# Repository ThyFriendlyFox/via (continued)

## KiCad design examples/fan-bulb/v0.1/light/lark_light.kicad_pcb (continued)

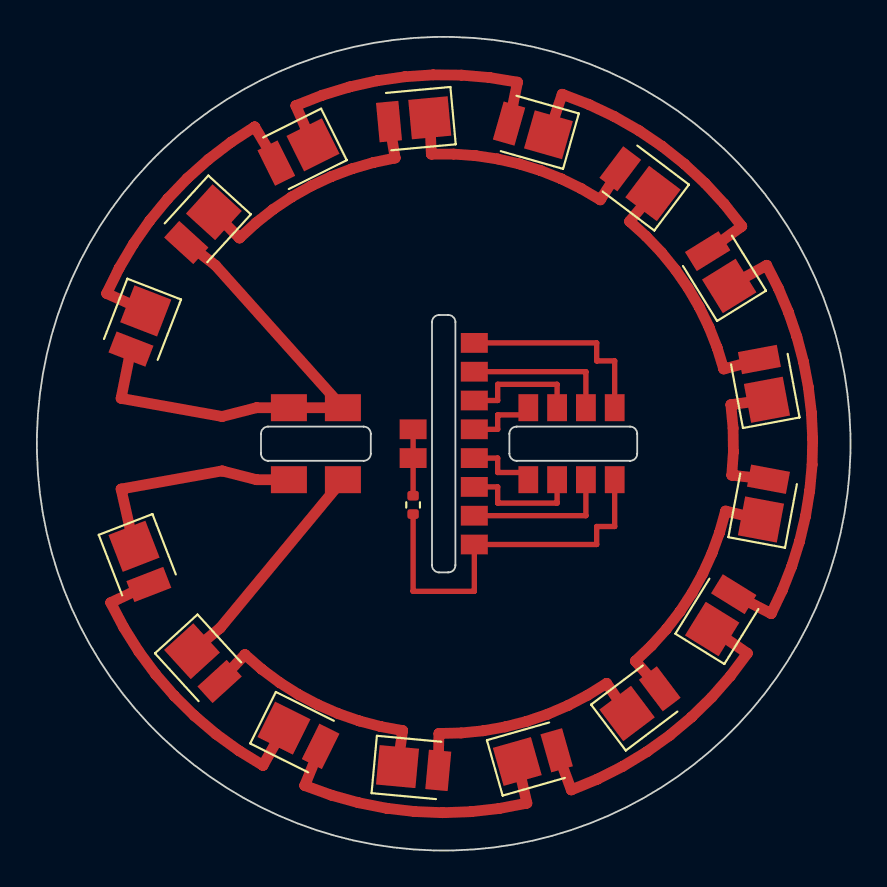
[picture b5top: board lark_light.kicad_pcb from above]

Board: 2 copper layers, 45.2 x 45.2 mm, 23 parts (0 on the bottom side), 26 nets.

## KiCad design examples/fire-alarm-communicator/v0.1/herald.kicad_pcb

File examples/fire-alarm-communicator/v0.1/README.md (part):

# Herald v0.1: a fire alarm communicator

Herald sits in a cabinet beside a fire alarm control panel and reports what the panel reports to a
monitoring station: over LTE-M first, over Wi-Fi when the cell path is down. It takes the panel's
signals 2 ways. It answers the panel's own phone dialer as if it were the phone line, and it reads
3 supervised relay contacts. A relay tells the panel when Herald itself is in trouble.

This folder is a whole KiCad 10 project made with Via: `design.py` is the board,
and the `.kicad_*` files beside it are what `workcenter design` writes from it. It is one of
Via's example projects, laid out the way a board repository lays out a version.

<!-- pictures:begin -->

| Front | Back |
|---|---|
|  |  |

| Every layer | The schematic, wired, in blocks |
|---|---|
|  |  |

From `workcenter render . --strict --views schematic,3d,layers,spin --width 1600 --spin-zoom 1.1`,
with KiCad's 3D bodies in `KICAD10_3DMODEL_DIR` (Via's `site/media/README.md` says how to
fetch them) and the 3 bodies in `models/`.
<!-- pictures:end -->

## What is hard about it, and where each part lives

| The problem | The answer on this board |
|---|---|
| A fire panel reports by phone, and there is no phone line | J2 is the panel dialer's line. Q3 (BCP53) and Q4 (MMBT3906) feed it a current-limited loop from the 24 V input: Q4 holds 0.55-0.75 V across R18 (27 ohm), 20 to 28 mA. R22 (47 ohm) in the return reads the loop current, so the ESP32 sees the dialer go off hook. The ESP32 then plays dial tone, the handshake and the kissoff from a PWM pin through 2 RC poles (R25-R27, C26-C28), and hears the dialer's DTMF digits on an ADC pin through C29 and R28 onto a mid-rail bias. `sim/tone_out.cir` and `sim/dtmf_in.cir` hold each level at every corner. |
| DTMF without a DTMF chip | `firmware/src/dtmf.c` runs a Goertzel filter per DTMF frequency over 25.6 ms windows, 12.8 ms apart, at 8 kHz. It takes and refuses what ITU-T Q.24 (Table A-1) says a receiver must: 0 to -25 dBm, the high tone 4 dB over to 8 dB under the low one, 1.5 % off frequency but not 3.5 %, 40 ms digits but not 23 ms ones. The host tests play all 16 keys and a whole Contact ID call through it. |
| A panel that reports by relay | 3 supervised inputs on J3. Each loop ends in a 4.7k resistor across the panel's contact, so the ADC tells a closed contact, a whole loop and a cut wire apart. R32 (4.7k) pulls each loop up, R31 (100) meets the field wiring, U8 clamps it. `sim/zone_*.cir` hold every reading 200 mV or more from the firmware's thresholds at every corner. |
| The panel must know when Herald fails | K1 (Omron G6K-2F-Y) is held on while Herald is healthy. A lost supply opens it, and so does a reset: R46 holds Q6 off until the firmware drives it. The panel sees its supervisory or trouble input change. Both poles run in parallel. |
| 2 paths to the station | U3, a Quectel BG95-M1 (LTE-M), with its nano SIM (J5) and antenna connector (J4). The ESP32-S3's own Wi-Fi is the second path; its antenna is on the module's u.FL. The BG95's I/O is 1.8 V: U4 (TXS0104E) carries its UART, STATUS and RI to the ESP32's 3.3 V. |
| When neither path works | Q5 (LINE_EN) lets the firmware drop the line feed. The panel then sees no phone line and reports its own communication trouble, the way it would for a cut line. R21 holds the feed off while the ESP32 is in reset. |
| The panel's 0 V must not touch the cabinet | A fire panel watches for an earth fault: any path from its wiring to earth. The 4 mounting holes are bare, and nothing ties GND to them. The back of the board says so. |

## The board

- 84.4 x 64 mm, 4 layers, 1.6 mm: F.Cu signal and a GND pour, In1.Cu a whole GND plane, In2.Cu
  signal, B.Cu signal and a GND pour. Every part is on the front. Order it as 4 layers.
- Red solder mask, white legend, ENIG: `design.py`'s `HeraldDesign` writes the colours into the
  stackup, and `workcenter render` draws the board in them.
- The field wiring enters along the bottom edge: 24 V in, the phone line, the 3 inputs and their
  common, the trouble relay's contacts, and the cabinet's tamper switch. Each terminal block's
  wire entry faces the edge.
- The status lights (power, cell, Wi-Fi, alarm, trouble), the USB-C port for set-up and the TEST
  and RESET buttons sit on the right edge; the LTE antenna connector in the top-left corner.
- The antenna feed from the BG95's pad 60 to J4 is drawn by hand, 0.35 mm: 50 ohm over In1.Cu.

### Power

J1 takes the panel's 24 V auxiliary output, 18 to 28 V. F1 (a PTC) and D1 (SMAJ28A) come first: a
surge is clamped, and a supply wired backwards drives D1 forward until F1 trips. D2 (SS34) keeps the
reversed voltage off everything else. U1 (LMR33630, 3 A, 400 kHz) makes +3V8 for the modem; U2
(TLV75733P, 1 A) makes +3V3 from it. The BG95 makes its own +1V8 (VDD_EXT) for its I/O. USB's
5 V reaches the buck through D3, so the board runs on a laptop for set-up. R3 and R4 let the ESP32
read the input.

### The ESP32-S3's pins

| GPIO | Net | To |
|---|---|---|
| 0 | IO0 | the boot strap, held high by R14 |
| 1, 2, 4 | ZONE1_ADC, ZONE2_ADC, ZONE3_ADC | the 3 inputs (ADC1 channels 0, 1, 3) |
| 3 | IO3 | a strapping pin with no pull of its own, held low by R17 |
| 5 | LOOP_ADC | the off-hook sense, R23 from RING (ADC1 channel 4) |
| 6 | VSENSE | the 24 V input through R3/R4 (ADC1 channel 5) |
| 7 | DTMF_ADC | the DTMF input (ADC1 channel 6) |
| 8, 9 | PWRKEY_CTL, RESET_CTL | Q1 and Q2, the BG95's PWRKEY and RESET_N |
| 10, 11 | ESP_TXD, ESP_RXD | the BG95's UART through U4 |
| 12, 13 | STATUS_3V3, RI_3V3 | the BG95's STATUS and RI through U4 |
| 14 | TONE | the tone path (LEDC PWM) |
| 15 | LINE_EN | Q5: the line feed on |
| 16 | RELAY_DRV | Q6: the trouble relay |
| 17 | TAMPER | J8, the cabinet's tamper switch |
| 19, 20 | USB_DN, USB_DP | J6 through U7 |
| 35-38 | LED_CELL, LED_WIFI, LED_ALARM, LED_TRBL | D8-D11 |
| 39 | BTN_TEST | SW1 |

The checks beside the table (`PROCESSES.md` P16): every analog input is on ADC1, because ADC2 is
shared with Wi-Fi (ESP-IDF, "ADC Oneshot", Hardware Limitations). GPIO26 is the PSRAM's on the
N4R2 variant and is left free (datasheet v1.7, Table 3-1, note b). GPIO45 and GPIO46 are straps and
are left to their internal pull-downs (Table 4-1). GPIO3 must not float (section 4.4): R17.

### Connectors

| Ref | Part | Pins |
|---|---|---|
| J1 | Phoenix PT 1,5/ 2-3,5-H BK, 3.5 mm, 2-way, black | 1 +24V (VFACP), 2 0V |
| J2 | Phoenix PT 1,5/ 2-3,5-H BK, 3.5 mm, 2-way, black | 1 TIP (through F2), 2 RING |
| J3 | Phoenix PT 1,5/ 4-3,5-H BK, 3.5 mm, 4-way, black | 1 ALM, 2 SUP, 3 TBL, 4 0V: the 3 loops' common |
| J7 | Phoenix PT 1,5/ 3-3,5-H BK, 3.5 mm, 3-way, black | 1 NC, 2 C, 3 NO of K1 (C to NO closed while healthy) |
| J8 | Phoenix PT 1,5/ 2-3,5-H BK, 3.5 mm, 2-way, black | 1 TAMP, 2 0V: the cabinet door's switch, closed while shut |
| J6 | GCT USB4085, through-hole | VBUS through D3 to the buck, D+/D- to the ESP32, CC1/CC2 5.1k to GND (a device) |
| J4 | Hirose U.FL | the BG95's main antenna |
| J5 | Same Sky NSIM-2-C, hinged | the BG95's USIM: VCC, RST, CLK, I/O through 22 ohm (R9-R11) |

## The call

What the dialer and Herald say to each other, with the firmware's constant for each
(`firmware/src/contactid.h`). The SIA DC-05 text was not read: the values come from 2 open
receivers (spandsp's `ademco_contactid.c`, Asterisk's `app_alarmreceiver.c`), the Zeta ZNDC fire
dialer's manual (5.2-5.3) and DMP's LT-1462, which cites DC-05-1999.09.

| Step | Who | What |
|---|---|---|
| Seize | the dialer | goes off hook: the loop current reads 0.78 V or more on GPIO5 for 20 ms (`LINE_STABLE`) |
| Dial tone | Herald | North America's 350 + 440 Hz, until the first digit |
| Dial | the dialer | the station's number in DTMF; 1.5 s of quiet ends it (`DIAL_GAP_MS`) |
| Handshake | Herald | 1400 Hz 100 ms, silence 100 ms, 2300 Hz 100 ms |
| Message | the dialer | 16 DTMF digits, 50-60 ms on and off: ACCT MT Q XYZ GG CCC S. The values' sum, 0 counted as 10, is a multiple of 15; 11-15 go as `*`, `#`, `A`, `B`, `C` |
| Kissoff | Herald | 1400 Hz for 800 ms after a good message (`KISSOFF_MS`); none after a bad one, so the dialer sends it again |

Fire panels' common event codes: 110 fire alarm, 200 fire supervisory, 300 system trouble, 301 AC
loss, 373 fire trouble, 602 periodic test (Q 1 a new event, 3 a restore).

## What proves it

```sh
workcenter design design.py --route    # the KiCad project, routed: from this folder
workcenter gates .                     # ERC, DRC, SIM, EXPORT
make -C firmware test                  # the inputs, the hook, DTMF and Contact ID on the host
```

- **The gates.** `GREEN with 7 warnings`: ERC 0 errors and 0 warnings; DRC 0 errors and 0
  unconnected, the 7 warnings the silkscreen of the 5 terminal blocks and the USB receptacle
  (2 lines) reaching the edge they face; SIM 8 decks, 573 corner runs; EXPORT 4 of 4 outputs,
  24 gerber files in `build/fab/`.
- **The route.** FreeRouting joins every net but 3, drawn by hand. It found no way for K1's NO
  contact past the strip that keeps tracks off the terminals' names, and took the C contact round
  the relay's label: both run on the front straight down to a via clear of the legend, then on
  In2.Cu under the strip to J7. Left to the router, D+ walled J6's A5 pin in, so CC1 runs from R15
  straight down and across into A5, between D+ and VBUS. A ground via beside 4 pads (U5.63,
  C24.2, J5.SH, C13.2) is placed before the route, so no route walls them off the front pour.
  `workcenter inspect probe` on the routed board finds each track clear and each via meeting only
  itself, and the DRC agrees. Keep-outs hold copper off every word: the front's
  under the mark, the terminals', the lights' and the buttons' names; the back's under the mark,
  the name, the subtitles, the write-on boxes and each terminal group's 2 lines.
- **The supervised inputs, simulated.** `sim/zone_short.cir`, `sim/zone_normal.cir`,
  `sim/zone_normal_wire.cir` and `sim/zone_open.cir` put a closed contact, a whole loop with and
  without 100 ohm of wire, and a cut wire on zone 1, each with 1 uA of leakage pushing toward the
  nearest threshold. The corners (`sim/corners.json`) run 0 and 50 C, every resistor at both ends
  of 1 %, the end-of-line resistor at 5 %, +3V3 at 3 %, and 32 Monte Carlo draws. The worst
  readings: a closed contact 0.151 V, a whole loop 1.555 to 1.798 V, a cut wire 3.186 V; each
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
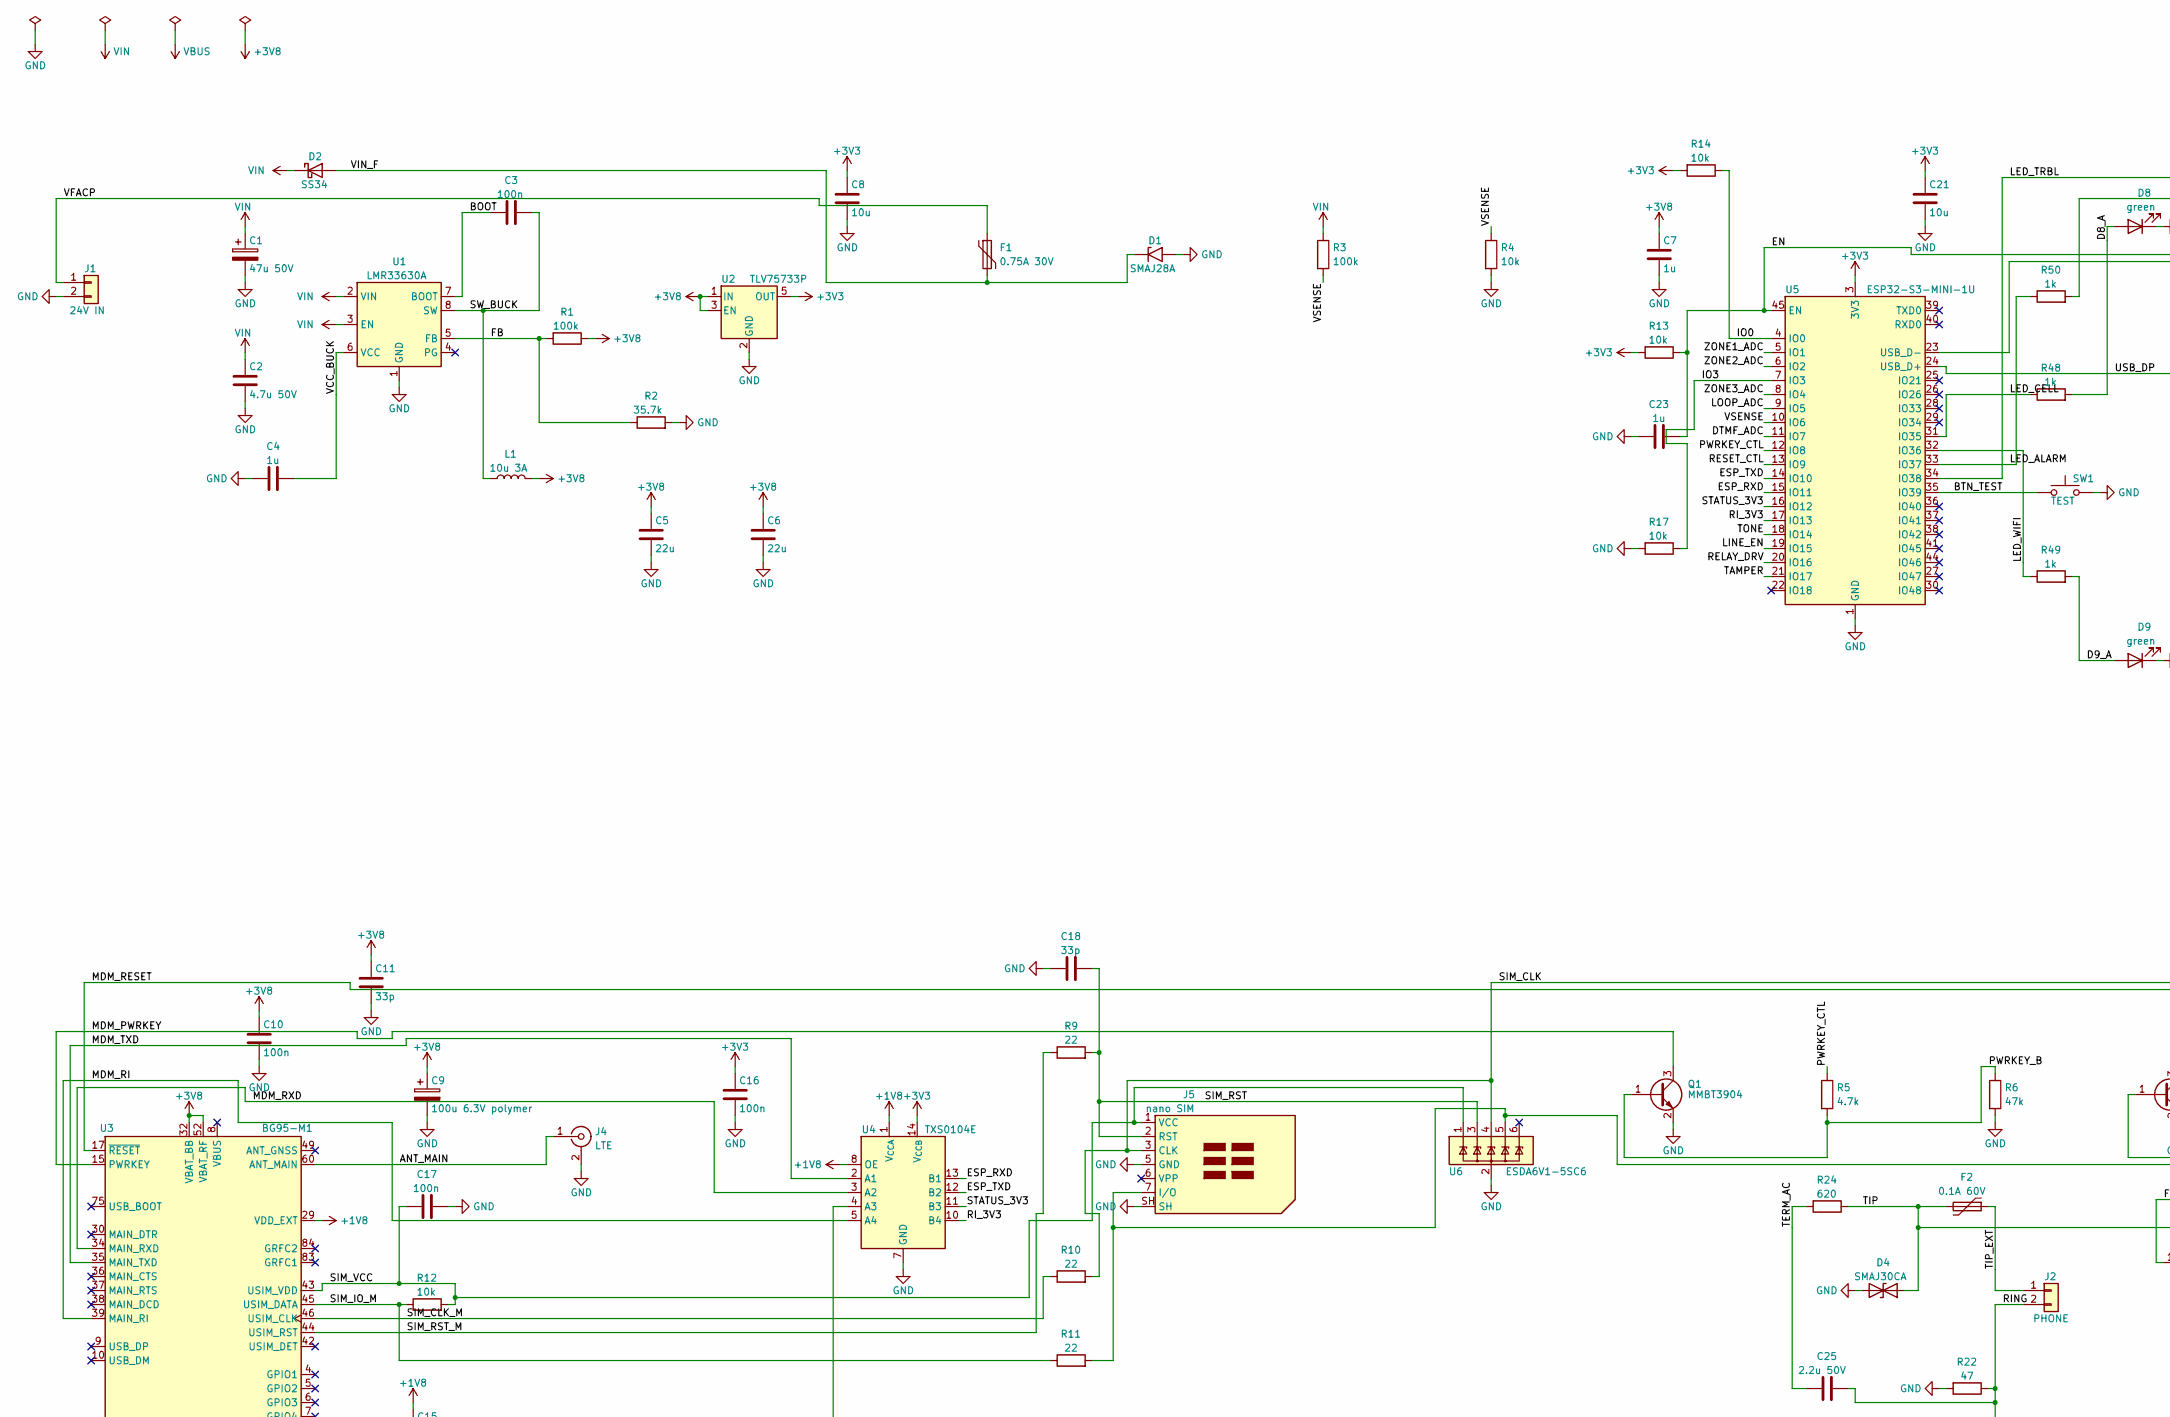
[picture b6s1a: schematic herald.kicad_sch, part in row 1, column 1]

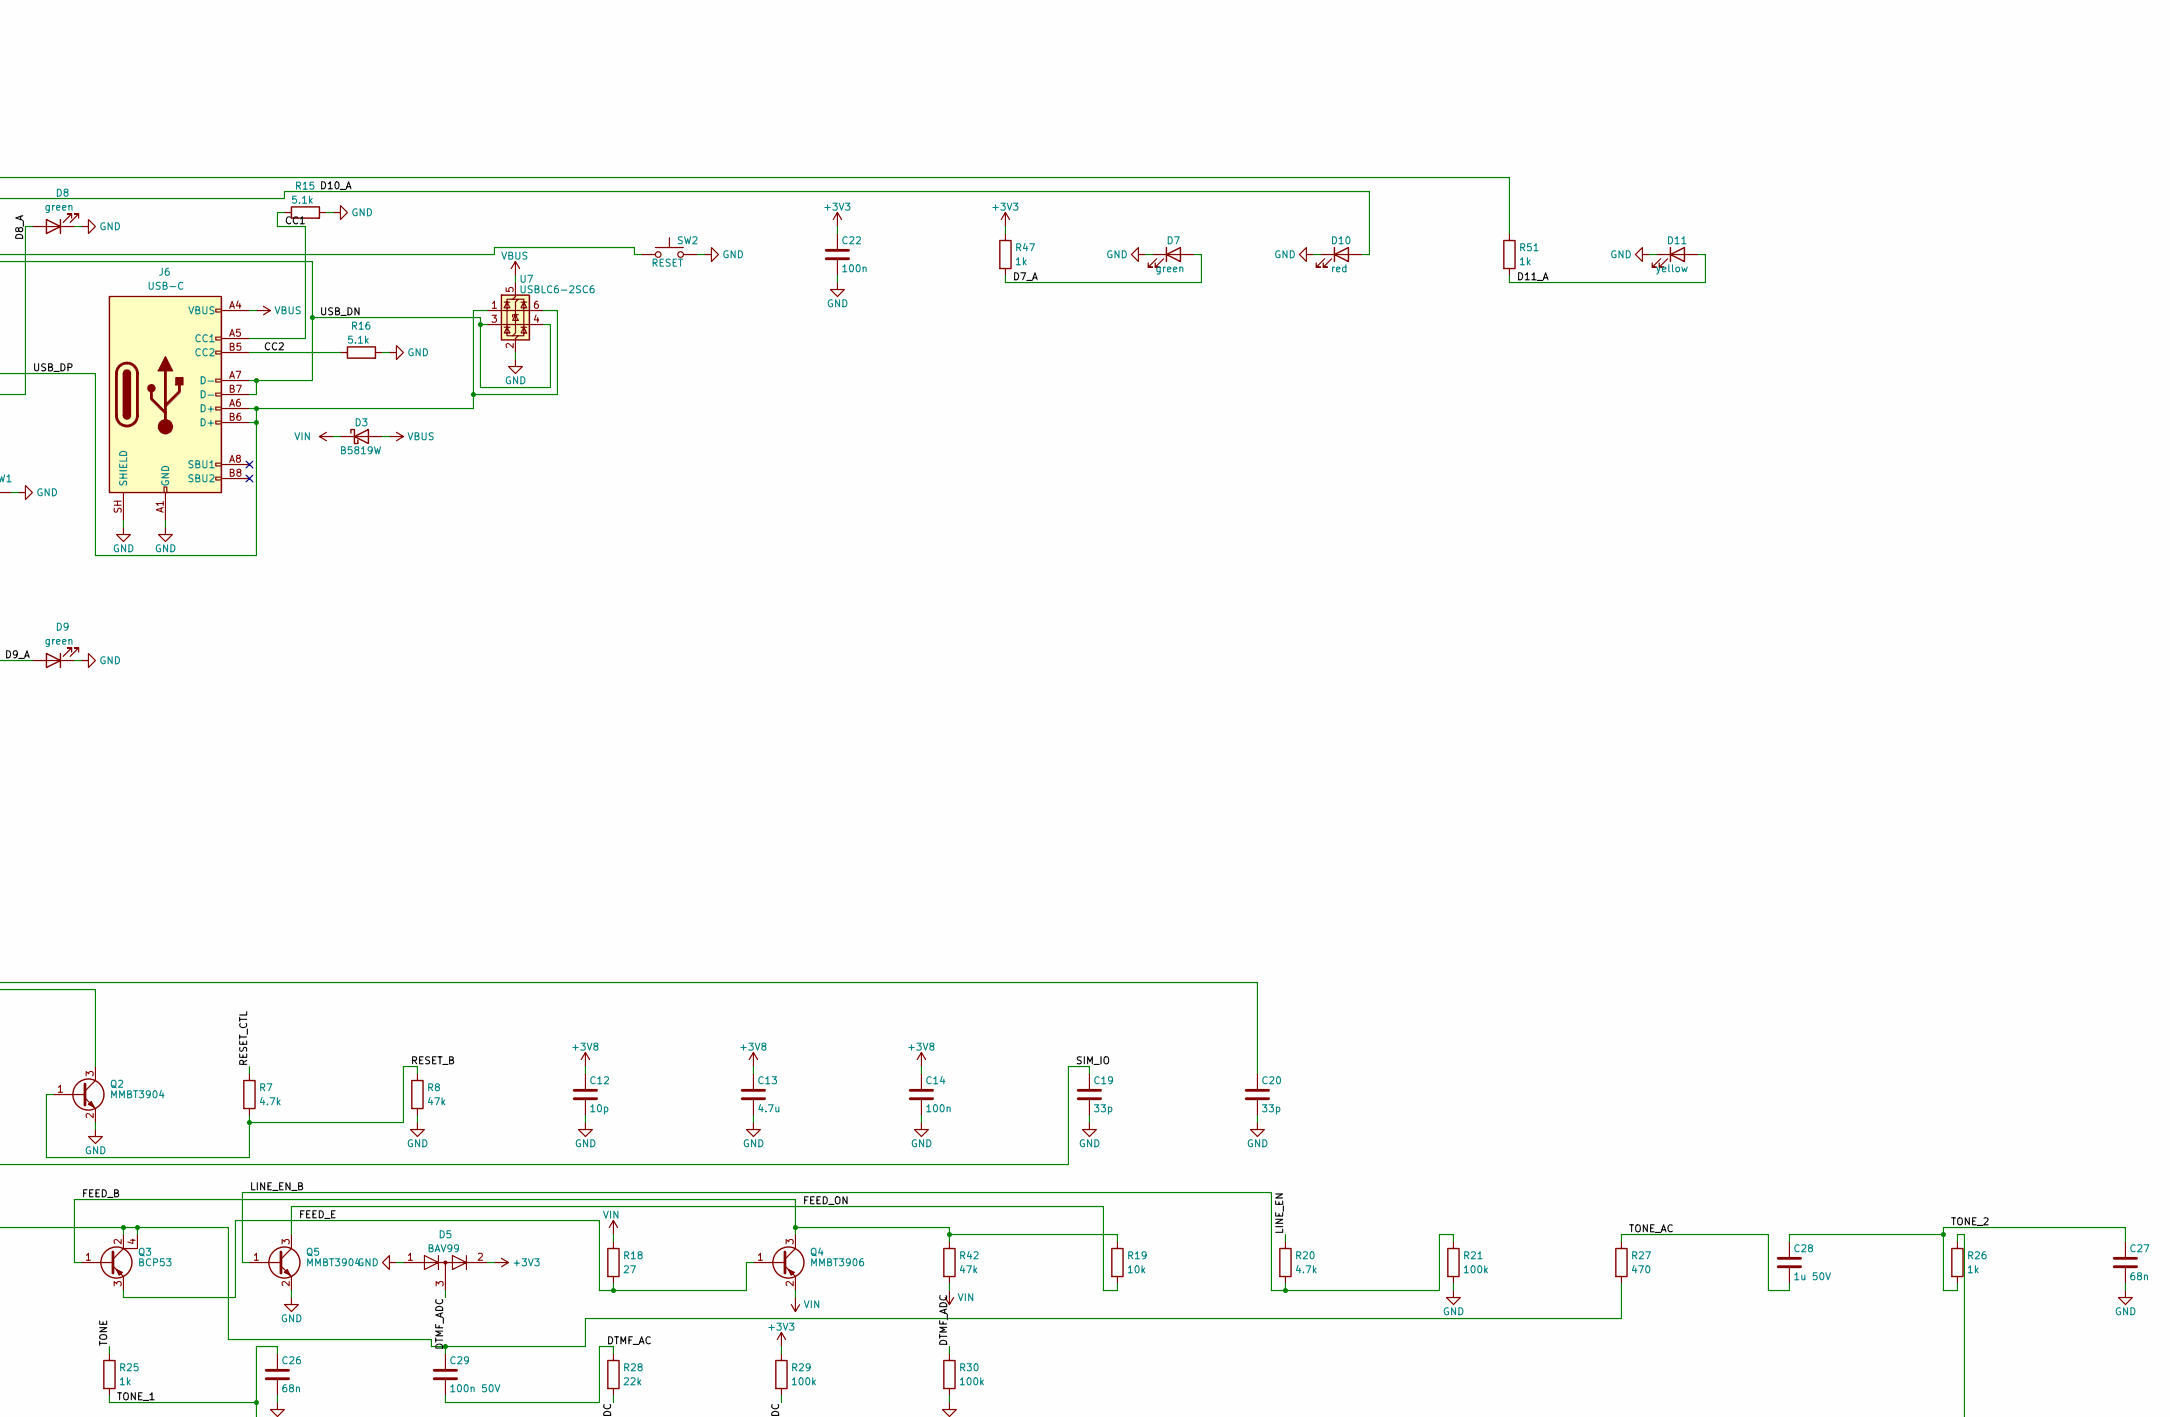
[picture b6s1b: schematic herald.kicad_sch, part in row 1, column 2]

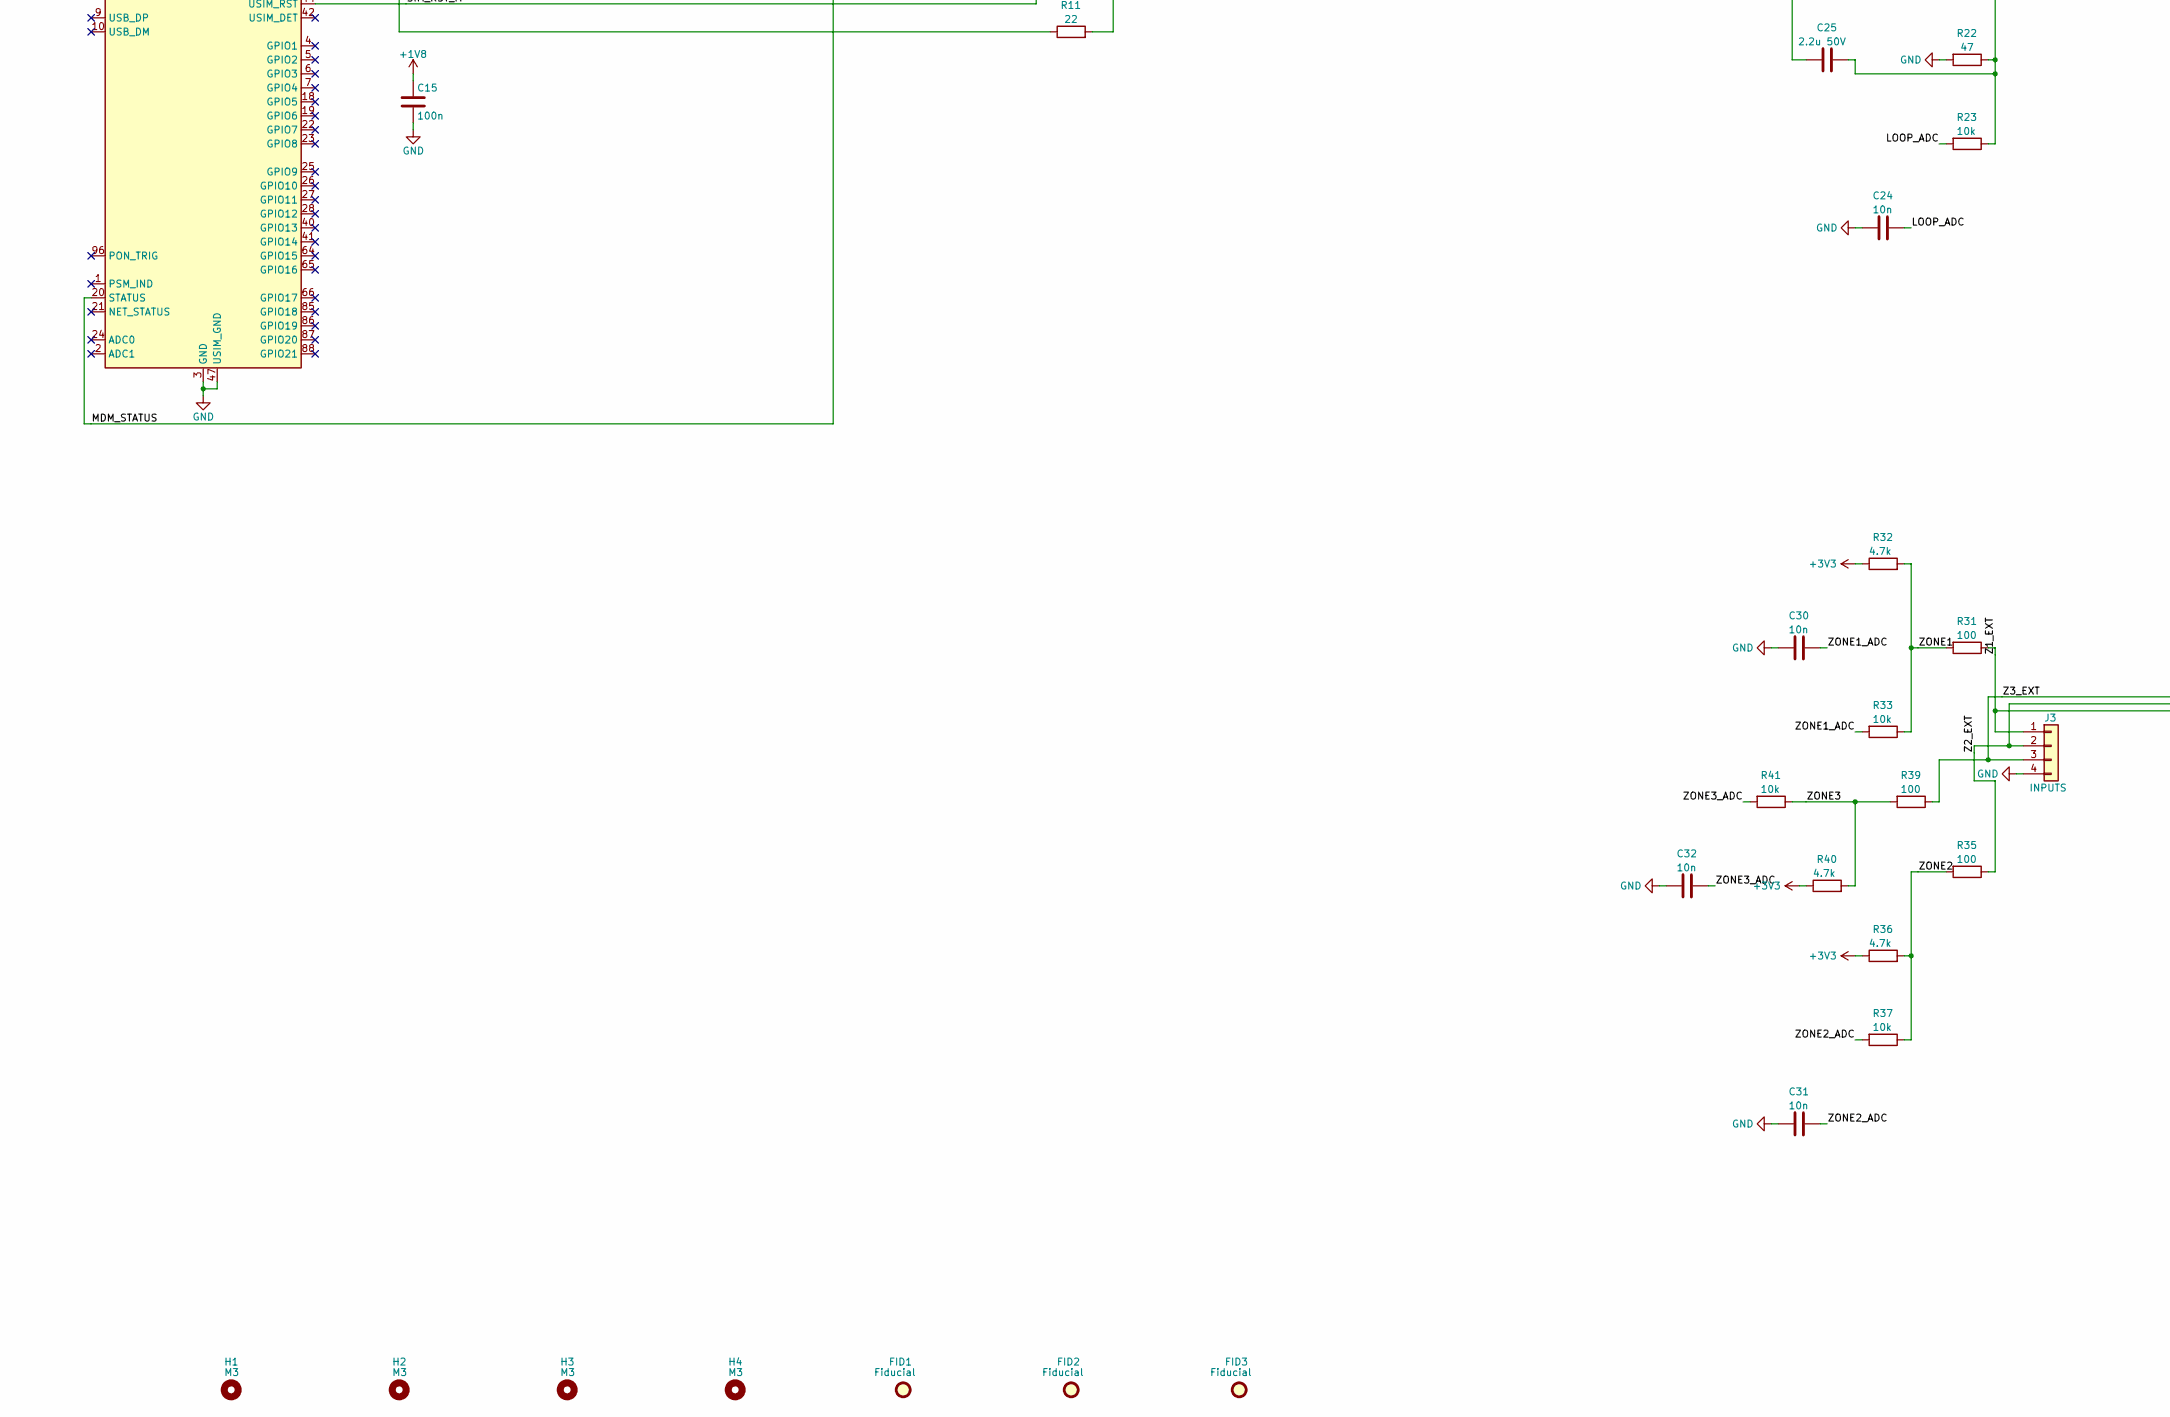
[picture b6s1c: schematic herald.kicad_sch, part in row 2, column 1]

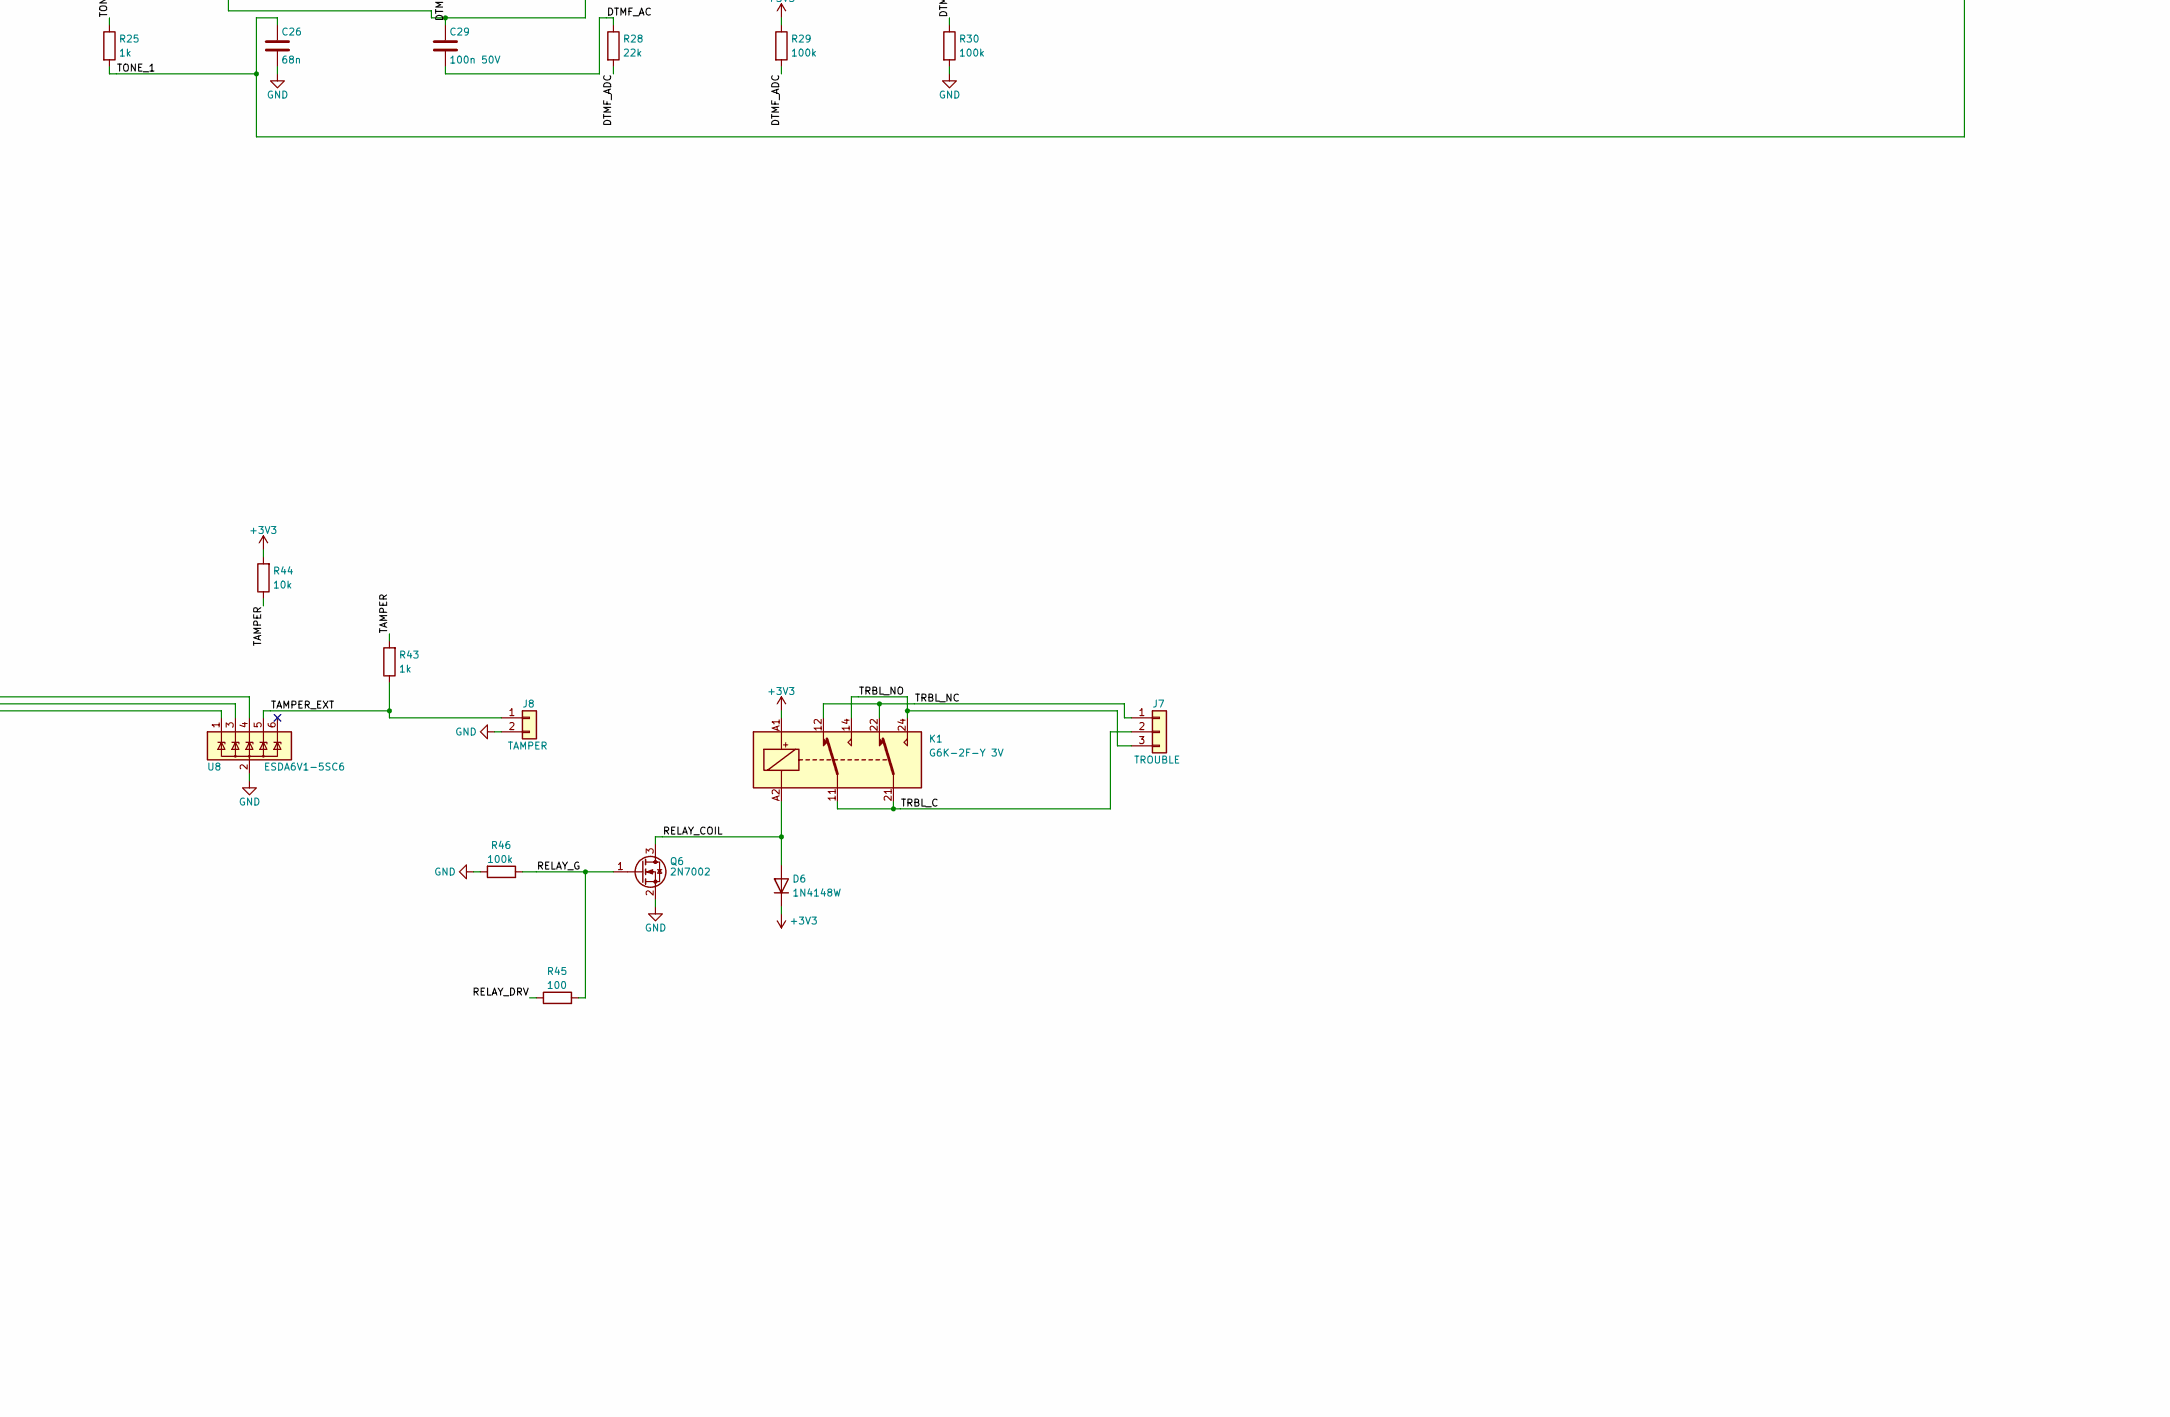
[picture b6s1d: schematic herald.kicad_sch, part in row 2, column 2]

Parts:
C1: 47u 50V; CP_Elec_6.3x7.7
C2: 4.7u 50V; C_1210_3225Metric
C3, C10, C14, C15, C16, C17, C22: 100n; C_0402_1005Metric
C4, C7, C23: 1u; C_0402_1005Metric
C5, C6: 22u; C_0805_2012Metric
C8, C21: 10u; C_0603_1608Metric
C9: 100u 6.3V polymer; CP_EIA-3528-21_Kemet-B
C11, C18, C19, C20: 33p; C_0402_1005Metric
C12: 10p; C_0402_1005Metric
C13: 4.7u; C_0603_1608Metric
C24, C30, C31, C32: 10n; C_0402_1005Metric
C25: 2.2u 50V; C_1206_3216Metric
C26, C27: 68n; C_0402_1005Metric
C28: 1u 50V; C_0805_2012Metric
C29: 100n 50V; C_0603_1608Metric
D1: SMAJ28A; D_SMA
D2: SS34; D_SMA
D3: B5819W; D_SOD-123
D4: SMAJ30CA; D_SMA
D5: BAV99; SOT-23
D6: 1N4148W; D_SOD-123
D7, D8, D9: green; LED_0603_1608Metric
D10: red; LED_0603_1608Metric
D11: yellow; LED_0603_1608Metric
F1: 0.75A 30V; Fuse_1206_3216Metric
F2: 0.1A 60V; Fuse_1206_3216Metric
FID1, FID2, FID3: Fiducial; Fiducial_1mm_Mask2mm
H1, H2, H3, H4: M3; MountingHole_3.2mm_M3
J1: 24V IN; TerminalBlock_Phoenix_PT-1,5-2-3.5-H_1x02_P3.50mm_Horizontal
J2: PHONE; TerminalBlock_Phoenix_PT-1,5-2-3.5-H_1x02_P3.50mm_Horizontal
J3: INPUTS; TerminalBlock_Phoenix_PT-1,5-4-3.5-H_1x04_P3.50mm_Horizontal
J4: LTE; U.FL_Hirose_U.FL-R-SMT-1_Vertical
J5: nano SIM; nanoSIM_Hinged_CUI_NSIM-2-C
J6: USB-C; USB_C_Receptacle_GCT_USB4085
J7: TROUBLE; TerminalBlock_Phoenix_PT-1,5-3-3.5-H_1x03_P3.50mm_Horizontal
J8: TAMPER; TerminalBlock_Phoenix_PT-1,5-2-3.5-H_1x02_P3.50mm_Horizontal
K1: G6K-2F-Y 3V; Relay_DPDT_Omron_G6K-2F-Y
L1: 10u 3A; L_Bourns_SRN6045TA
Q1, Q2, Q5: MMBT3904; SOT-23
Q3: BCP53; SOT-223
Q4: MMBT3906; SOT-23
Q6: 2N7002; SOT-23
R1, R3, R21, R29, R30, R46: 100k; R_0402_1005Metric
R2: 35.7k; R_0402_1005Metric
R4, R12, R13, R14, R17, R23, R33, R37, R41, R44: 10k; R_0402_1005Metric
R5, R7, R20, R32, R36, R40: 4.7k; R_0402_1005Metric
R6, R8, R42: 47k; R_0402_1005Metric
R9, R10, R11: 22; R_0402_1005Metric
R15, R16: 5.1k; R_0402_1005Metric
R18: 27; R_0805_2012Metric
R19: 10k; R_0603_1608Metric
R22: 47; R_0805_2012Metric
R24: 620; R_0805_2012Metric
R25, R26, R43, R47, R48, R49, R50, R51: 1k; R_0402_1005Metric
R27: 470; R_0603_1608Metric
R28: 22k; R_0402_1005Metric
R31, R35, R39: 100; R_0603_1608Metric
R45: 100; R_0402_1005Metric
SW1: TEST; SW_SPST_PTS810
SW2: RESET; SW_SPST_PTS810
U1: LMR33630A; HSOP-8-1EP_3.9x4.9mm_P1.27mm_EP2.41x3.1mm
U2: TLV75733P; SOT-23-5
U3: BG95-M1; Quectel_BG95
U4: TXS0104E; TSSOP-14_4.4x5mm_P0.65mm
U5: ESP32-S3-MINI-1U; ESP32-S2-MINI-1U
U6, U8: ESDA6V1-5SC6; SOT-23-6
U7: USBLC6-2SC6; SOT-23-6

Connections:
+1V8: C15.1, U3.29 (VDD_EXT), U4.1 (V_{CCA}), U4.8 (OE)
+3V3: C8.1, C16.1, C21.1, C22.1, D5.2 (A), D6.1 (K), K1.A1, R13.2, R14.2, R29.1, R32.1, R36.1, R40.1, R44.2, R47.1, U2.5 (OUT), U4.14 (V_{CCB}), U5.3 (3V3)
+3V8: C5.1, C6.1, C7.1, C9.1, C10.1, C11.1, C12.1, C13.1, C14.1, L1.2, R1.1, U2.1 (IN), U2.3 (EN), U3.32 (VBAT_BB), U3.33 (VBAT_BB), U3.52 (VBAT_RF), U3.53 (VBAT_RF)
/ANT_MAIN: J4.1 (In), U3.60 (ANT_MAIN)
/BOOT: C3.1, U1.7 (BOOT)
/BTN_TEST: SW1.1, U5.35 (IO39)
/CC1: J6.A5 (CC1), R15.1
/CC2: J6.B5 (CC2), R16.1
/D7_A: D7.2 (A), R47.2
/D8_A: D8.2 (A), R48.2
/D9_A: D9.2 (A), R49.2
/D10_A: D10.2 (A), R50.2
/D11_A: D11.2 (A), R51.2
/DTMF_AC: C29.2, R28.1
/DTMF_ADC: D5.3 (K), R28.2, R29.2, R30.1, U5.11 (IO7)
/EN: C23.1, R13.1, SW2.1, U5.45 (EN)
/ESP_RXD: U4.13 (B1), U5.15 (IO11)
/ESP_TXD: U4.12 (B2), U5.14 (IO10)
/FB: R1.2, R2.1, U1.5 (FB)
/FEED_B: Q3.1 (B), Q4.3 (C), R19.1, R42.1
/FEED_E: Q3.3 (E), Q4.1 (B), R18.2
/FEED_ON: Q5.3 (C), R19.2
/IO0: R14.1, U5.4 (IO0)
/IO3: R17.1, U5.7 (IO3)
/LED_ALARM: R50.1, U5.33 (IO37)
/LED_CELL: R48.1, U5.31 (IO35)
/LED_TRBL: R51.1, U5.34 (IO38)
/LED_WIFI: R49.1, U5.32 (IO36)
/LINE_EN: R20.1, U5.19 (IO15)
/LINE_EN_B: Q5.1 (B), R20.2, R21.1
/LOOP_ADC: C24.1, R23.2, U5.9 (IO5)
/MDM_PWRKEY: Q1.3 (C), U3.15 (PWRKEY)
/MDM_RESET: Q2.3 (C), U3.17 (~RESET)
/MDM_RI: U3.39 (MAIN_RI), U4.5 (A4)
/MDM_RXD: U3.34 (MAIN_RXD), U4.3 (A2)
/MDM_STATUS: U3.20 (STATUS), U4.4 (A3)
/MDM_TXD: U3.35 (MAIN_TXD), U4.2 (A1)
/PWRKEY_B: Q1.1 (B), R5.2, R6.1
/PWRKEY_CTL: R5.1, U5.12 (IO8)
/RELAY_COIL: D6.2 (A), K1.A2, Q6.3 (D)
/RELAY_DRV: R45.1, U5.20 (IO16)
/RELAY_G: Q6.1 (G), R45.2, R46.1
/RESET_B: Q2.1 (B), R7.2, R8.1
/RESET_CTL: R7.1, U5.13 (IO9)
/RING: C25.2, J2.2, R22.1, R23.1
/RI_3V3: U4.10 (B4), U5.17 (IO13)
/SIM_CLK: C20.1, J5.3 (CLK), R10.2, U6.4 (IO3)
/SIM_CLK_M: R10.1, U3.46 (USIM_CLK)
/SIM_IO: C19.1, J5.7 (I/O), R11.2, U6.5 (IO4)
/SIM_IO_M: R11.1, R12.1, U3.45 (USIM_DATA)
/SIM_RST: C18.1, J5.2 (RST), R9.2, U6.3 (IO2)
/SIM_RST_M: R9.1, U3.44 (USIM_RST)
/SIM_VCC: C17.1, J5.1 (VCC), R12.2, U3.43 (USIM_VDD), U6.1 (IO1)
/STATUS_3V3: U4.11 (B3), U5.16 (IO12)
/SW_BUCK: C3.2, L1.1, U1.8 (SW)
/TAMPER: R43.2, R44.1, U5.21 (IO17)
/TAMPER_EXT: J8.1, R43.1, U8.5 (IO4)
/TERM_AC: C25.1, R24.2
/TIP: C29.1, D4.1 (A1), F2.2, Q3.2 (C), Q3.4 (C), R24.1, R27.2
/TIP_EXT: F2.1, J2.1
/TONE: R25.1, U5.18 (IO14)
/TONE_1: C26.1, R25.2, R26.1
/TONE_2: C27.1, C28.1, R26.2
/TONE_AC: C28.2, R27.1
/TRBL_C: J7.2, K1.11, K1.21
/TRBL_NC: J7.1, K1.12, K1.22
/TRBL_NO: J7.3, K1.14, K1.24
/USB_DN: J6.A7 (D-), J6.B7 (D-), U5.23 (USB_D-), U7.3 (I/O2), U7.4 (I/O2)
/USB_DP: J6.A6 (D+), J6.B6 (D+), U5.24 (USB_D+), U7.1 (I/O1), U7.6 (I/O1)
/VCC_BUCK: C4.1, U1.6 (VCC)
/VFACP: F1.1, J1.1
/VIN_F: D1.1 (A1), D2.2 (A), F1.2
/VSENSE: R3.2, R4.1, U5.10 (IO6)
/Z1_EXT: J3.1, R31.1, U8.1 (IO1)
/Z2_EXT: J3.2, R35.1, U8.3 (IO2)
/Z3_EXT: J3.3, R39.1, U8.4 (IO3)
/ZONE1: R31.2, R32.2, R33.1
/ZONE1_ADC: C30.1, R33.2, U5.5 (IO1)
/ZONE2: R35.2, R36.2, R37.1
/ZONE2_ADC: C31.1, R37.2, U5.6 (IO2)
/ZONE3: R39.2, R40.2, R41.1
/ZONE3_ADC: C32.1, R41.2, U5.8 (IO4)
GND: C1.2, C2.2, C4.2, C5.2, C6.2, C7.2, C8.2, C9.2, C10.2, C11.2, C12.2, C13.2, C14.2, C15.2, C16.2, C17.2, C18.2, C19.2, C20.2, C21.2, C22.2, C23.2, C24.2, C26.2, C27.2, C30.2, C31.2, C32.2, D1.2 (A2), D4.2 (A2), D5.1 (K), D7.1 (K), D8.1 (K), D9.1 (K), D10.1 (K), D11.1 (K), J1.2, J3.4, J4.2 (Ext), J5.5 (GND), J5.SH, J6.A1 (GND), J6.A12 (GND), J6.B1 (GND), J6.B12 (GND), J6.SH (SHIELD), J8.2, Q1.2 (E), Q2.2 (E), Q5.2 (E), Q6.2 (S), R2.2, R4.2, R6.2, R8.2, R15.2, R16.2, R17.2, R21.2, R22.2, R30.2, R46.2, SW1.2, SW2.2, U1.1 (GND), U1.9 (GND), U2.2 (GND), U3.3 (GND), U3.31 (GND), U3.47 (USIM_GND), U3.48 (GND), U3.50 (GND), U3.54 (GND), U3.55 (GND), U3.58 (GND), U3.59 (GND), U3.61 (GND), U3.62 (GND), U3.67 (GND), U3.68 (GND), U3.69 (GND), U3.70 (GND), U3.71 (GND), U3.72 (GND), U3.73 (GND), U3.74 (GND), U3.79 (GND), U3.80 (GND), U3.81 (GND), U3.82 (GND), U3.89 (GND), U3.90 (GND), U3.91 (GND), U3.100 (GND), U3.101 (GND), U3.102 (GND), U4.7 (GND), U5.1 (GND), U5.2 (GND), U5.42 (GND), U5.43 (GND), U5.46 (GND), U5.47 (GND), U5.48 (GND), U5.49 (GND), U5.50 (GND), U5.51 (GND), U5.52 (GND), U5.53 (GND), U5.54 (GND), U5.55 (GND), U5.56 (GND), U5.57 (GND), U5.58 (GND), U5.59 (GND), U5.60 (GND), U5.61 (GND), U5.62 (GND), U5.63 (GND), U5.64 (GND), U5.65 (GND), U6.2 (GND), U7.2 (GND), U8.2 (GND)
VBUS: D3.2 (A), J6.A4 (VBUS), J6.A9 (VBUS), J6.B4 (VBUS), J6.B9 (VBUS), U7.5 (VBUS)
VIN: C1.1, C2.1, D2.1 (K), D3.1 (K), Q4.2 (E), R3.1, R18.1, R42.2, U1.2 (VIN), U1.3 (EN)

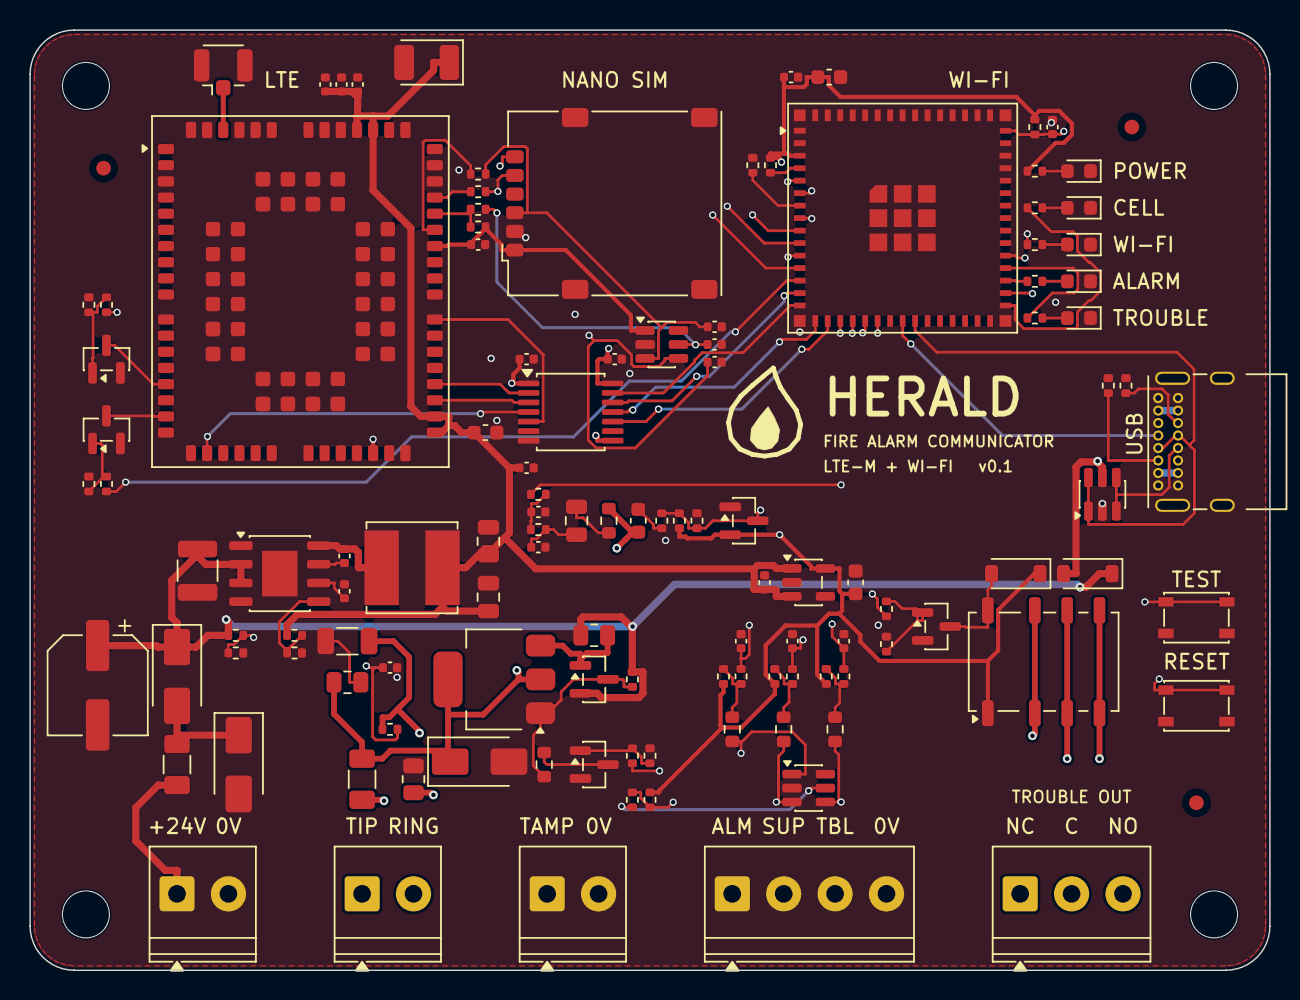
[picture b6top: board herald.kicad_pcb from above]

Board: 4 copper layers, 84.4 x 64.0 mm, 127 parts (0 on the bottom side), 85 nets.

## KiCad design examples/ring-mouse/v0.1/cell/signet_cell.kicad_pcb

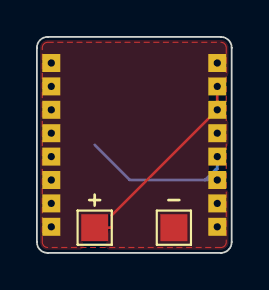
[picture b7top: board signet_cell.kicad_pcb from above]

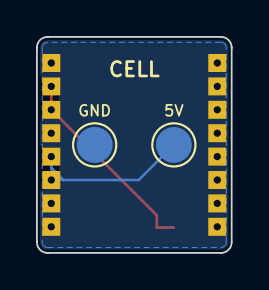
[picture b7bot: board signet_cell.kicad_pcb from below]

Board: 2 copper layers, 10.8 x 12.0 mm, 6 parts (2 on the bottom side), 3 nets.

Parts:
J1: CLICKS; Joint_Edge_1x08_P1.3mm
J2: POWER; Joint_Edge_1x08_P1.3mm
TP1: BAT+; TestPoint_Pad_1.5x1.5mm
TP2: BAT-; TestPoint_Pad_1.5x1.5mm
TP3: VCHG; TestPoint_Pad_D2.0mm
TP4: GND; TestPoint_Pad_D2.0mm

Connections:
GND: J1.1, J1.2, J1.3, J1.4, J1.5, J1.6, J1.7, J1.8, J2.1, J2.4, J2.7, J2.8, TP2.1, TP4.1
VBAT: J2.2, J2.3, TP1.1
VCHG: J2.5, J2.6, TP3.1

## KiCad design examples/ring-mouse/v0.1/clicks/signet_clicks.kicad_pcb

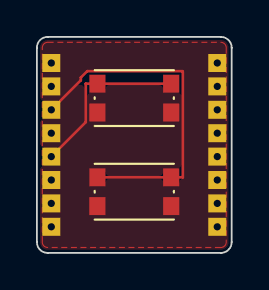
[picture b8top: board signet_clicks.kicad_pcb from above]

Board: 2 copper layers, 10.8 x 12.0 mm, 4 parts (0 on the bottom side), 3 nets.

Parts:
J1: TOUCH; Joint_Edge_1x08_P1.3mm
J2: CELL; Joint_Edge_1x08_P1.3mm
SW1: LEFT; SW_Push_1P1T_NO_CK_KMR2
SW2: RIGHT; SW_Push_1P1T_NO_CK_KMR2

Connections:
/BTN_L: J1.5, SW1.1
/BTN_R: J1.3, SW2.1
GND: J1.1, J1.2, J1.4, J1.6, J1.7, J1.8, J2.1, J2.2, J2.3, J2.4, J2.5, J2.6, J2.7, J2.8, SW1.2, SW2.2
